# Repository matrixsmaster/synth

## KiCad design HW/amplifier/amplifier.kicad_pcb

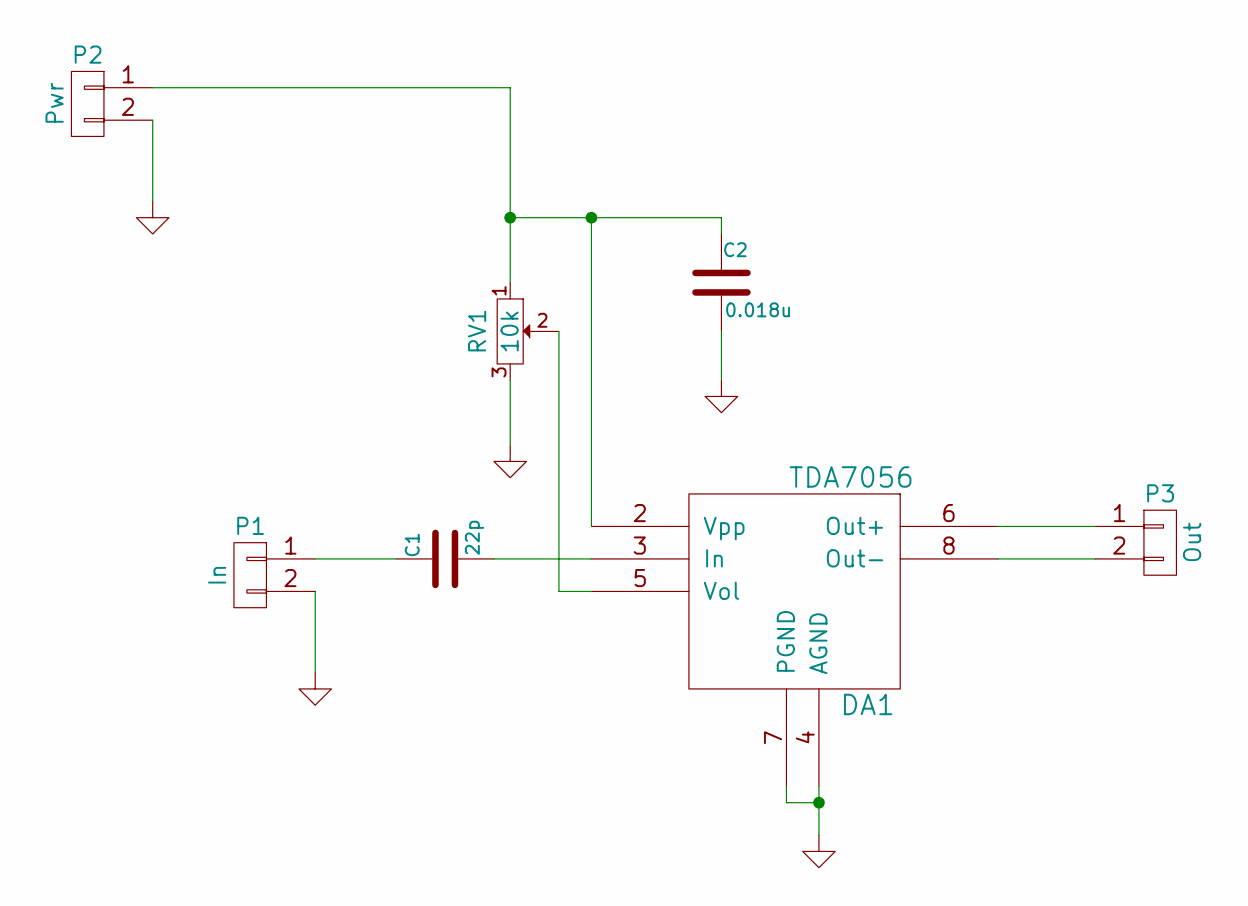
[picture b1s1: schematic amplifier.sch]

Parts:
C1: 22p; R3
C2: 0.018u; R3
DA1: TDA7056; SIL-9
P1: In; PIN_ARRAY_2X1
P2: Pwr; PIN_ARRAY_2X1
P3: Out; PIN_ARRAY_2X1
RV1: 10k; RV2

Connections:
GND: C2.2, DA1.4 (AGND), DA1.7 (PGND), P1.2, P2.2, RV1.3
unnamed: C1.1, P1.1
unnamed: C1.2, DA1.3 (In)
unnamed: C2.1, DA1.2 (Vpp), P2.1, RV1.1
unnamed: DA1.5 (Vol), RV1.2
unnamed: DA1.6 (Out+), P3.1
unnamed: DA1.8 (Out-), P3.2

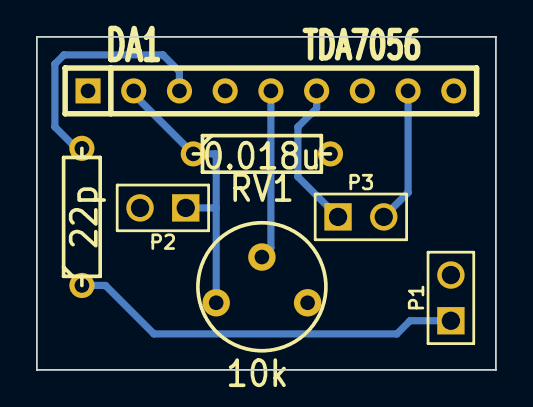
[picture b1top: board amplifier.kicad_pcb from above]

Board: 2 copper layers, 25.5 x 18.5 mm, 7 parts (0 on the bottom side), 7 nets.

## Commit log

2019-03-24 SW: added preliminary code for stm32f429-discovery board
2019-03-24 HW: added audio amplifier board schematics and routing
2019-03-30 SW: added SDL2 demo project for waveform experiments
2019-04-07 HW: Analog synth1: fixed error in schematics after some real testing
